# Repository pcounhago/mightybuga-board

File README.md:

# Mighty Bug-A Control board

Control board for the line follower racing car project designed at [A Industriosa](https://intranet.aindustriosa.org/).

## Releases

Version | Description | Status
------------ | ------------- | ------------
[v1](v1/README.md) | Initial board design. Has a mayor supply problem with the AMS1117-3.3 regulator. **Do not use unless you replace the regulator with a more capable one.** | Released
[v1.1](v1.1/README.md) | Updated version of v1 that solves the supply problems by replacing the regulator with a MP2307DN. | Released
[v2](v2/README.md) | Lighter version of the v1.1 redesigned to improve weight distribution in the car. | Released
[v2.1](v2.1/README.md) | Even lighter version of the control board. Include SWIO interface for programming and debug purposes. Fix some minor issues found in v2. | Released

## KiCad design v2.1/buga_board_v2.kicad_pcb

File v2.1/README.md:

# Mighty Bug-A Board v2.1

Control board for the line follower racing car project designed at [A Industriosa](https://intranet.aindustriosa.org/).

* Check the 3D printed chassis designs at [https://gitlab.com/punkto/line_follower_3d_designs](https://gitlab.com/punkto/line_follower_3d_designs)

* For the firmware refer to [https://github.com/hmightypirate/AllMyCircuits](https://github.com/hmightypirate/AllMyCircuits)

## Description

Designed to control a line follower racing car based on differential drive, this board includes an STM32F103 microcontroller coupled with a TB6612FNG dual channel motor driver and a U3V12F9 step-up regulator to power two Pololu micro metal gearmotors at stable 9V. The board provides headers to connect the motors using the magnetic encoder boards mounted on them.

To detect the position of the line, a QTR-8A array featuring 8 Fairchild QRE1113 reflectance sensors is connected to the right angle header mounted on the front.

2 LEDs, 2 push buttons and a buzzer are provided to configure the board and give feedback while the car is on the track.

There is also a UART header that can be used to program the microcontroller and to establish a communication link through cable or Bluetooth if an HC-05 adapter is used.

To expand the capabilities of the board, I2C and SPI buses are available on a header so that other hardware (like an IMU or a slave microcontroller) can be added at any time.

## BOM

Reference | Description | Quantity
------------ | ------------- | ------------- |
BZ1 | MLT-5020 SMD buzzer | 1
C1, C14 | 0805 ceramic capacitor, 1uF | 2
C10, C11 | 0805 ceramic capacitor, 20pF | 2
C12, C13, C15, C16, C17, C19, C21 | 0805 ceramic capacitor, 100nF | 7
C2 | 0805 ceramic capacitor, 10uF | 1
C20, C22 | 0805 ceramic capacitor, 10uF | 2
C3 | 0805 ceramic capacitor, 56nF | 1
C4 | 0805 ceramic capacitor, 100pF | 1
C5 | 0805 ceramic capacitor, 3.9nF | 1
C6 | 10nF | 1
C7 | 15pF | 1
C8 | 22uF | 1
C9, C18 | 4.7uF | 2
D1 | B220A-13-F | 1
D2 | 1210 Green LED | 1
D3 | 1N4148 1210 diode | 1
D4 | 1210 Red LED | 1
D5 | 1210 Blue LED | 1
J1, JP2 | 2 pin 2.54mm vertical header | 2
J2, J6, J7 | JST B6B-ZR connector | 3
J3 | JST S11B-ZR | 1
J4 | JST B4B-ZR | 1
J5 | B5B-ZR | 1
JP1 | 3 pin 2.54mm straight header | 1
L1 | Taiyo Yuden_NR-60xx 4.7uH inductor | 1
L2 | Taiyo Yuden NR-50xx 10uH inductor | 1
Q1, Q2 | SI2369DS P-Channel 30V MOSFET, SOT-23 | 2
Q3 | S8050 NPN Transistor, SOT-23 | 1
R1, R6, R7, R9, R10, R13, R14, R15, R16, R19 | 0805 Resistor, 10k | 10
R11 | 0805 Resistor, 47k | 1
R12 | 0805 Resistor, 7.5k | 1
R17, R18 | 0805 Resistor, 100 | 2
R2, R3, R5, R20 | 0805 Resistor, 100K | 4
R4 | 0805 Resistor, 6.8k | 1
R8 | 0805 Resistor, 26.1k | 1
SW1 | PCM12 SPDT switch | 1
SW2, SW3 | TL3343 Push button | 2
U1 | MP2307DN | 1
U2 | SC4503 | 1
U3 | STM32F103C8T6 | 1
U4 | TB6612FNG | 1
Y1 | 5032 8Mhz crystal | 1

## Acknowledgements

This work was inspired by the great job done in the micromouse maze solving robot Bulebule by [Bulebots](https://github.com/Bulebots):

[https://github.com/Bulebots/bulebule](https://github.com/Bulebots/bulebule)

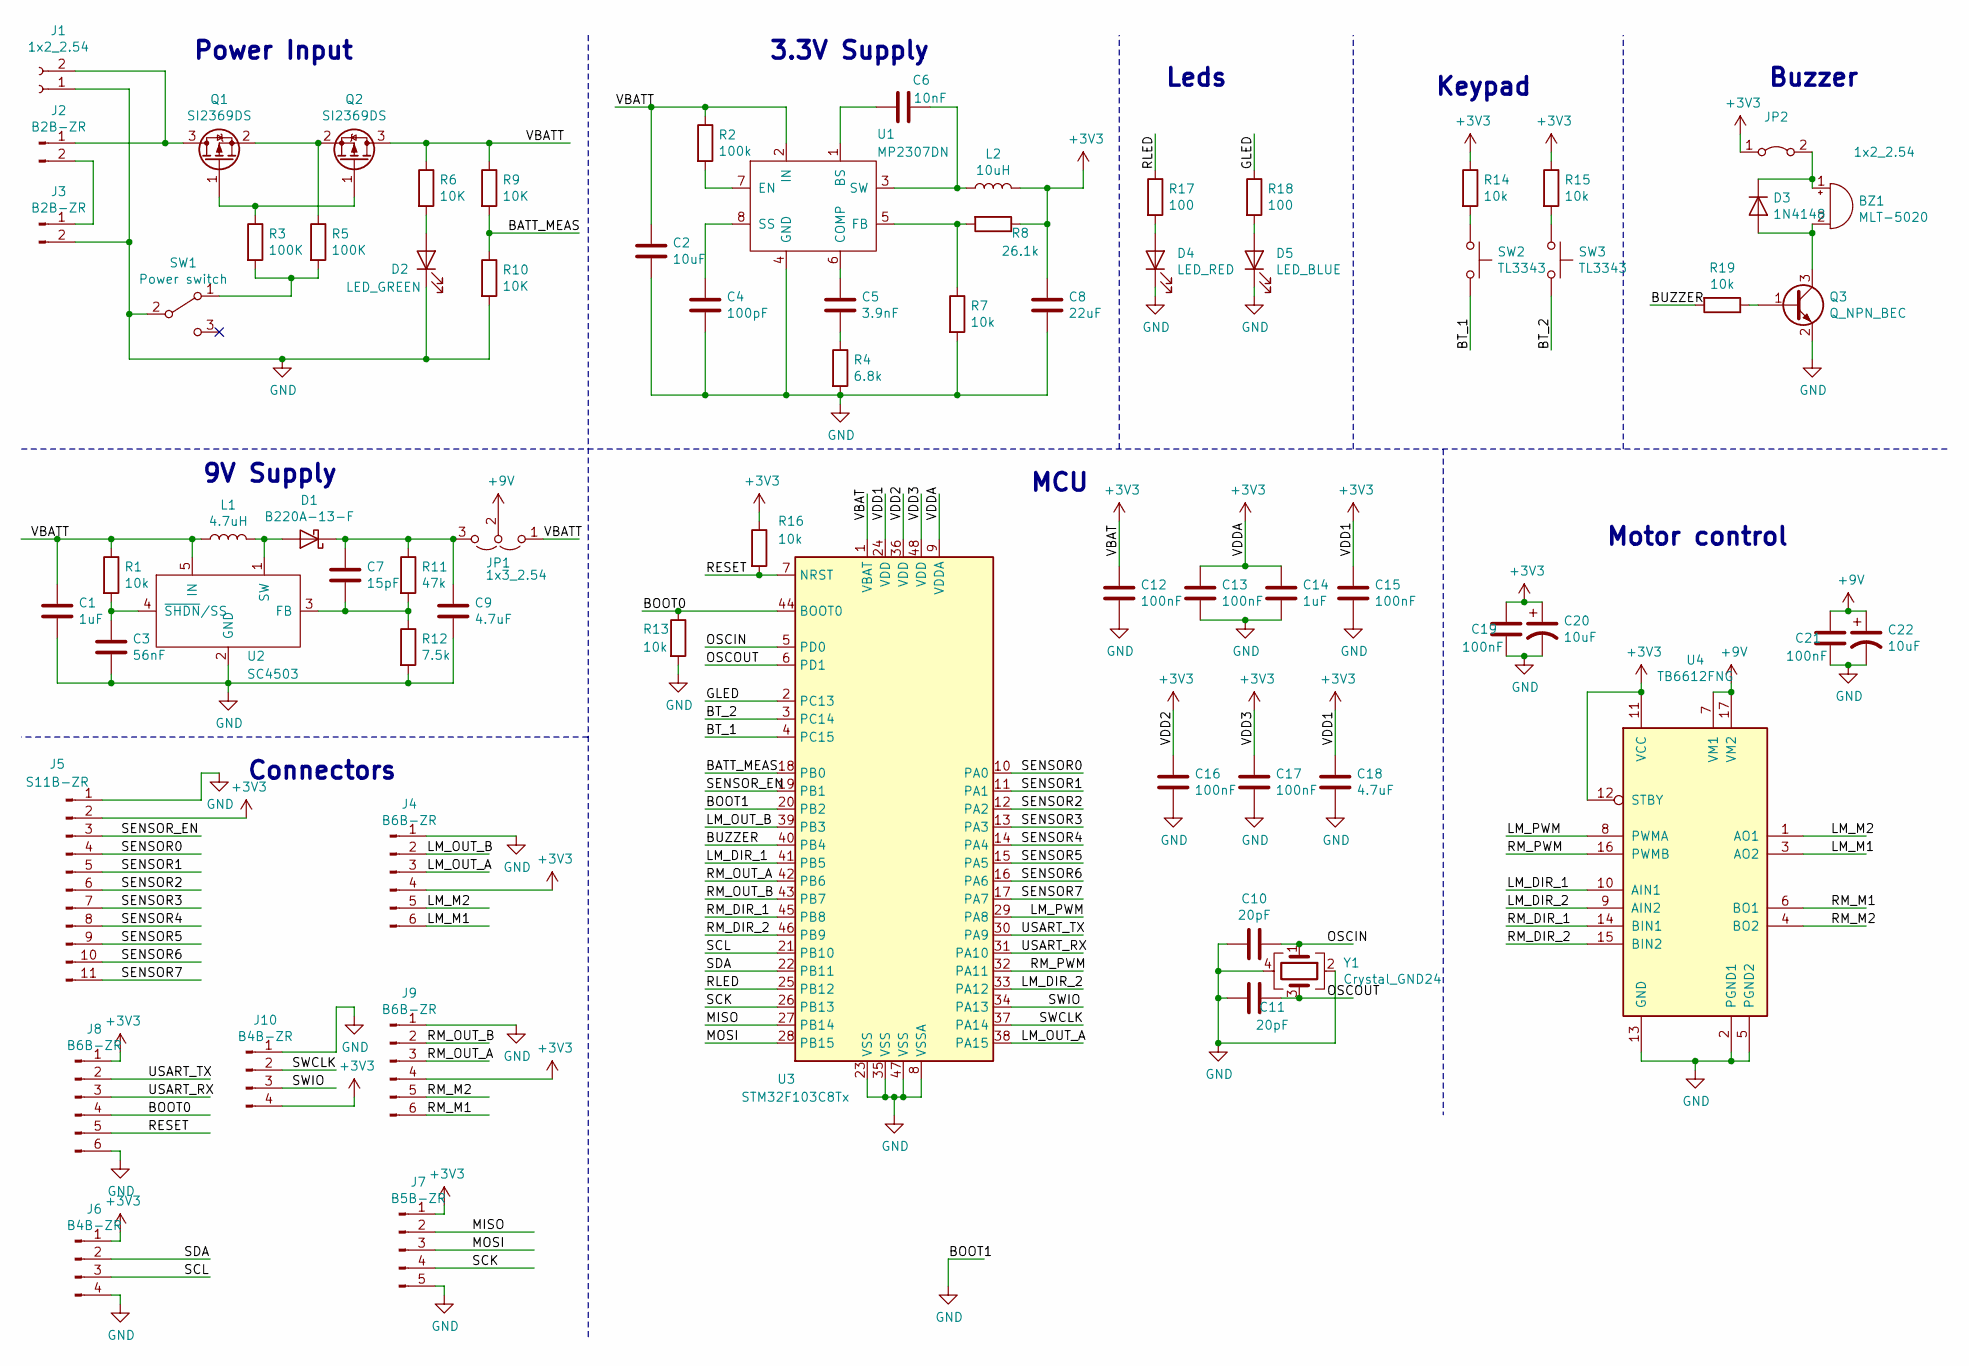
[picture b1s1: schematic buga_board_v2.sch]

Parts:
BZ1: MLT-5020
C1, C14: 1uF; C_0805_2012Metric_Pad1.15x1.40mm_HandSolder
C2: 10uF; C_0805_2012Metric_Pad1.15x1.40mm_HandSolder
C3: 56nF; C_0805_2012Metric_Pad1.15x1.40mm_HandSolder
C4: 100pF; C_0805_2012Metric_Pad1.15x1.40mm_HandSolder
C5: 3.9nF; C_0805_2012Metric_Pad1.15x1.40mm_HandSolder
C6: 10nF; C_0805_2012Metric_Pad1.15x1.40mm_HandSolder
C7: 15pF; C_0805_2012Metric_Pad1.15x1.40mm_HandSolder
C8: 22uF; C_0805_2012Metric_Pad1.15x1.40mm_HandSolder
C9, C18: 4.7uF; C_0805_2012Metric_Pad1.15x1.40mm_HandSolder
C10, C11: 20pF; C_0805_2012Metric_Pad1.15x1.40mm_HandSolder
C12, C13, C15, C16, C17, C19, C21: 100nF; C_0805_2012Metric_Pad1.15x1.40mm_HandSolder
C20, C22: 10uF; L_1210_3225Metric_Pad1.42x2.65mm_HandSolder
D1: B220A-13-F; D_SMA
D2: LED_GREEN; LED_1210_3225Metric_Pad1.42x2.65mm_HandSolder
D3: 1N4148; D_1210_3225Metric_Pad1.42x2.65mm_HandSolder
D4: LED_RED; LED_1210_3225Metric_Pad1.42x2.65mm_HandSolder
D5: LED_BLUE; LED_1210_3225Metric_Pad1.42x2.65mm_HandSolder
J1: 1x2_2.54; PinHeader_1x02_P2.54mm_Vertical
J2, J3: B2B-ZR
J4, J8, J9: B6B-ZR
J5: S11B-ZR
J6, J10: B4B-ZR
J7: B5B-ZR
JP1: 1x3_2.54; PinHeader_1x03_P2.54mm_Vertical
JP2: 1x2_2.54; PinHeader_1x02_P2.54mm_Vertical
L1: 4.7uH; L_Taiyo-Yuden_NR-60xx
L2: 10uH; L_Taiyo-Yuden_NR-50xx
Q1, Q2: SI2369DS; SOT-23
Q3: Q_NPN_BEC; SOT-23
R1, R7, R13, R14, R15, R16, R19: 10k; R_0805_2012Metric_Pad1.15x1.40mm_HandSolder
R2: 100k; R_0805_2012Metric_Pad1.15x1.40mm_HandSolder
R3, R5: 100K; R_0805_2012Metric_Pad1.15x1.40mm_HandSolder
R4: 6.8k; R_0805_2012Metric_Pad1.15x1.40mm_HandSolder
R6, R9, R10: 10K; R_0805_2012Metric_Pad1.15x1.40mm_HandSolder
R8: 26.1k; R_0805_2012Metric_Pad1.15x1.40mm_HandSolder
R11: 47k; R_0805_2012Metric_Pad1.15x1.40mm_HandSolder
R12: 7.5k; R_0805_2012Metric_Pad1.15x1.40mm_HandSolder
R17, R18: 100; R_0805_2012Metric_Pad1.15x1.40mm_HandSolder
SW1: Power switch; SW_SPDT_PCM12
SW2, SW3: TL3343; SW_SPST_TL3342
U1: MP2307DN; SOIC-8-1EP_3.9x4.9mm_P1.27mm_EP2.35x2.35mm
U2: SC4503; TSOT-23-5
U3: STM32F103C8Tx; LQFP-48_7x7mm_P0.5mm
U4: TB6612FNG; tb6612fng
Y1: Crystal_GND24; Crystal_SMD_5032-4Pin_5.0x3.2mm

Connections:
+3V3: C8.1, C12.1, C13.1, C14.1, C15.1, C16.1, C17.1, C18.1, C19.1, C20.1, J4.4, J5.2, J6.1, J7.1, J8.1, J9.4, J10.4, JP2.1 (A), L2.2, R8.1, R14.1, R15.1, R16.1, U3.1 (VBAT), U3.9 (VDDA), U3.24 (VDD), U3.36 (VDD), U3.48 (VDD), U4.11 (VCC), U4.12 (STBY)
+9V: C21.1, C22.1, JP1.2 (C), U4.7 (VM1), U4.17 (VM2)
/BATT_MEAS: R9.2, R10.1, U3.18 (PB0)
/BOOT0: J8.4, R13.1, U3.44 (BOOT0)
/BT_1: SW2.2, U3.4 (PC15)
/BT_2: SW3.2, U3.3 (PC14)
/BUZZER: R19.2, U3.40 (PB4)
/GLED: R18.1, U3.2 (PC13)
/LM_DIR_1: U3.41 (PB5), U4.10 (AIN1)
/LM_DIR_2: U3.33 (PA12), U4.9 (AIN2)
/LM_M1: J4.6, U4.3 (AO2)
/LM_M2: J4.5, U4.1 (AO1)
/LM_OUT_A: J4.3, U3.38 (PA15)
/LM_OUT_B: J4.2, U3.39 (PB3)
/LM_PWM: U3.29 (PA8), U4.8 (PWMA)
/MISO: J7.2, U3.27 (PB14)
/MOSI: J7.3, U3.28 (PB15)
/OSCIN: C10.1, U3.5 (PD0), Y1.1
/OSCOUT: C11.1, U3.6 (PD1), Y1.3
/RESET: J8.5, R16.2, U3.7 (NRST)
/RLED: R17.1, U3.25 (PB12)
/RM_DIR_1: U3.45 (PB8), U4.14 (BIN1)
/RM_DIR_2: U3.46 (PB9), U4.15 (BIN2)
/RM_M1: J9.6, U4.6 (BO1)
/RM_M2: J9.5, U4.4 (BO2)
/RM_OUT_A: J9.3, U3.42 (PB6)
/RM_OUT_B: J9.2, U3.43 (PB7)
/RM_PWM: U3.32 (PA11), U4.16 (PWMB)
/SCK: J7.4, U3.26 (PB13)
/SCL: J6.3, U3.21 (PB10)
/SDA: J6.2, U3.22 (PB11)
/SENSOR0: J5.4, U3.10 (PA0)
/SENSOR1: J5.5, U3.11 (PA1)
/SENSOR2: J5.6, U3.12 (PA2)
/SENSOR3: J5.7, U3.13 (PA3)
/SENSOR4: J5.8, U3.14 (PA4)
/SENSOR5: J5.9, U3.15 (PA5)
/SENSOR6: J5.10, U3.16 (PA6)
/SENSOR7: J5.11, U3.17 (PA7)
/SENSOR_EN: J5.3, U3.19 (PB1)
/SWCLK: J10.2, U3.37 (PA14)
/SWIO: J10.3, U3.34 (PA13)
/USART_RX: J8.3, U3.31 (PA10)
/USART_TX: J8.2, U3.30 (PA9)
/VBATT: C1.1, C2.1, JP1.1 (A), L1.1, Q2.3 (D), R1.1, R2.1, R6.1, R9.1, U1.2 (IN), U2.5 (IN)
GND: C1.2, C2.2, C3.2, C4.2, C8.2, C9.2, C10.2, C11.2, C12.2, C13.2, C14.2, C15.2, C16.2, C17.2, C18.2, C19.2, C20.2, C21.2, C22.2, D2.1 (K), D4.1 (K), D5.1 (K), J1.1, J3.2, J4.1, J5.1, J6.4, J7.5, J8.6, J9.1, J10.1, Q3.2 (E), R4.2, R7.2, R10.2, R12.2, R13.2, SW1.2 (B), U1.4 (GND), U2.2 (GND), U3.8 (VSSA), U3.20 (PB2), U3.23 (VSS), U3.35 (VSS), U3.47 (VSS), U4.2 (PGND1), U4.5 (PGND2), U4.13 (GND), Y1.2, Y1.4
unnamed: BZ1.1 (-), D3.1 (K), JP2.2 (B)
unnamed: BZ1.2 (+), D3.2 (A), Q3.3 (C)
unnamed: C3.1, R1.2, U2.4 (~SHDN~/SS)
unnamed: C4.1, U1.8 (SS)
unnamed: C5.1, U1.6 (COMP)
unnamed: C5.2, R4.1
unnamed: C6.1, L2.1, U1.3 (SW)
unnamed: C6.2, U1.1 (BS)
unnamed: C7.1, C9.1, D1.1 (K), JP1.3 (B), R11.1
unnamed: C7.2, R11.2, R12.1, U2.3 (FB)
unnamed: D1.2 (A), L1.2, U2.1 (SW)
unnamed: D2.2 (A), R6.2
unnamed: D4.2 (A), R17.2
unnamed: D5.2 (A), R18.2
unnamed: J1.2, J2.1, Q1.3 (D)
unnamed: J2.2, J3.1
unnamed: Q1.1 (G), Q2.1 (G), R3.1
unnamed: Q1.2 (S), Q2.2 (S), R5.1
unnamed: Q3.1 (B), R19.1
unnamed: R2.2, U1.7 (EN)
unnamed: R3.2, R5.2, SW1.1 (A)
unnamed: R7.1, R8.2, U1.5 (FB)
unnamed: R14.2, SW2.1
unnamed: R15.2, SW3.1

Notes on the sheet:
Power Input
9V Supply
3.3V Supply
Motor control
Buzzer
Keypad
Leds
MCU
Connectors

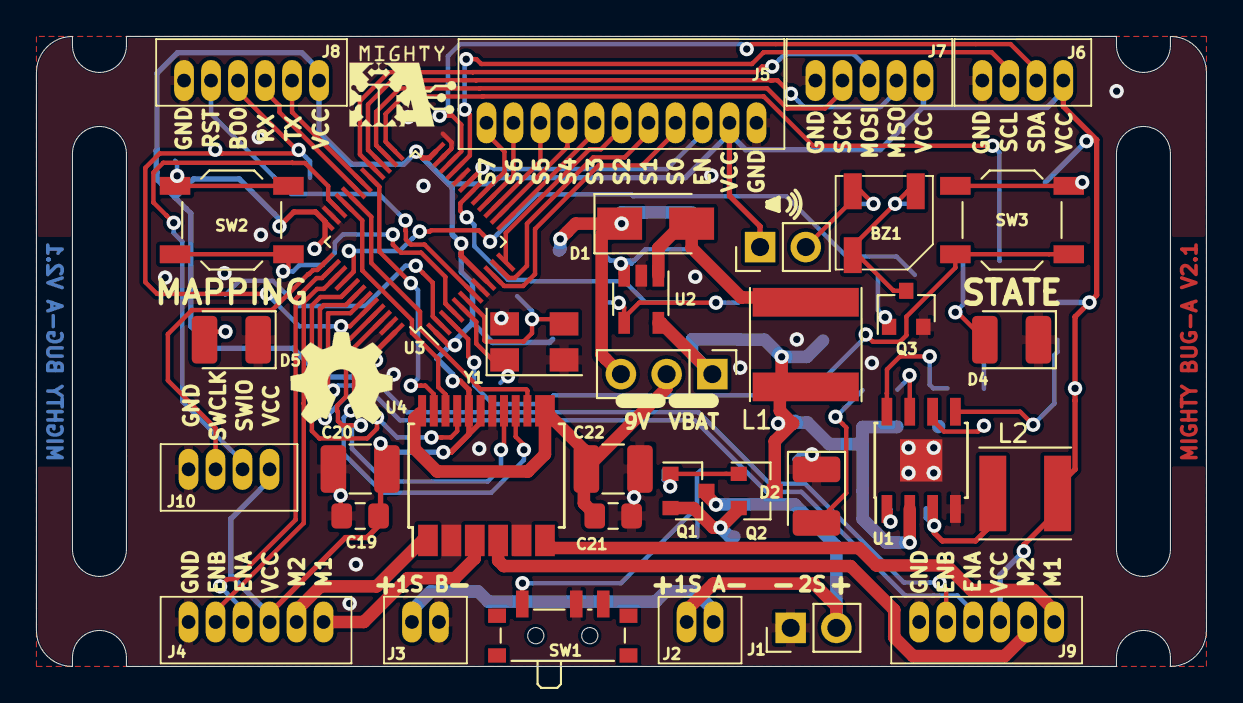
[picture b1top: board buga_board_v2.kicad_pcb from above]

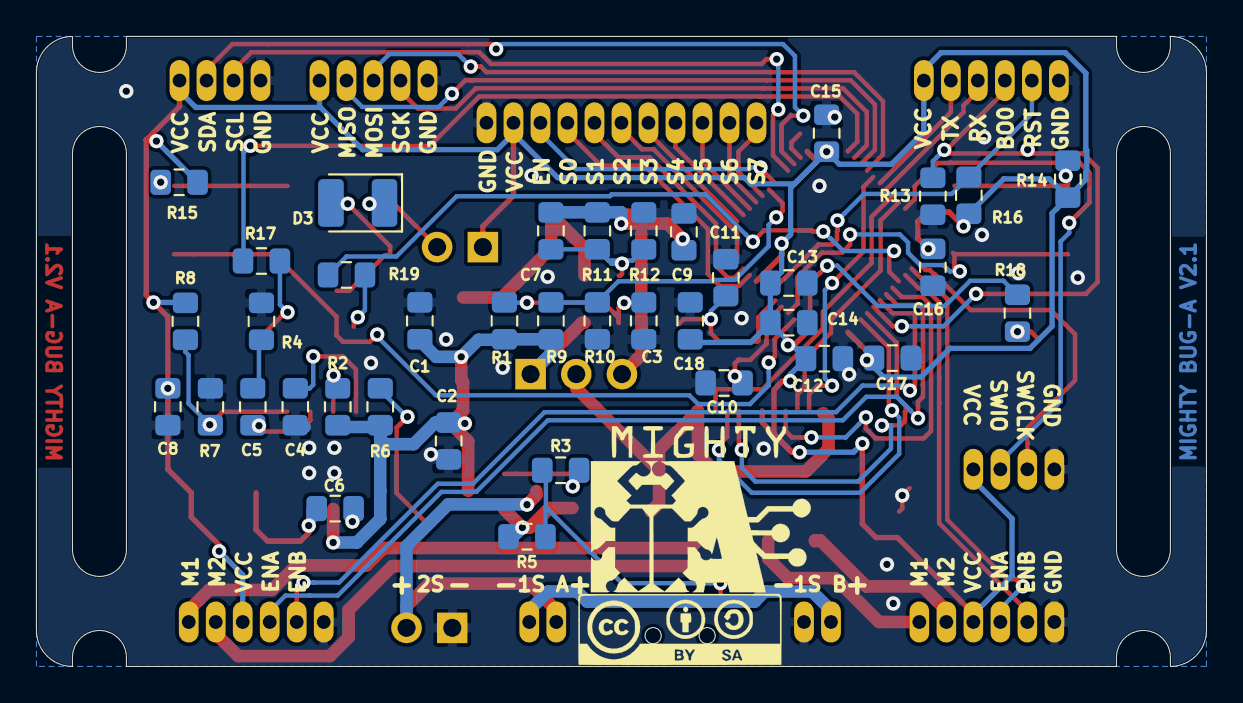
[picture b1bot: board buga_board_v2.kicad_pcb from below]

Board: 2 copper layers, 65.0 x 35.0 mm, 72 parts (38 on the bottom side), 70 nets.

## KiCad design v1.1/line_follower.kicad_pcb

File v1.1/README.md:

# Mighty Bug-A Board v1.1

Control board for the line follower racing car project designed at [A Industriosa](https://intranet.aindustriosa.org/).

* Check the 3D printed chassis designs at [https://gitlab.com/punkto/line_follower_3d_designs](https://gitlab.com/punkto/line_follower_3d_designs)

* For the firmware refer to [https://github.com/hmightypirate/AllMyCircuits](https://github.com/hmightypirate/AllMyCircuits)

## Description

Designed to control a line follower racing car based on differential drive, this board includes an STM32F103 microcontroller coupled with a TB6612FNG dual channel motor driver and a U3V12F9 step-up regulator to power two Pololu micro metal gearmotors at stable 9V. The board provides headers to connect the motors using the magnetic encoder boards mounted on them.

To detect the position of the line, a QTR-8A array featuring 8 Fairchild QRE1113 reflectance sensors is connected to the right angle header mounted on the front.

2 LEDs, 3 push buttons and a buzzer are provided to configure the board and give feedback while the car is on the track.

There is also a UART header that can be used to program the microcontroller and to establish a communication link through cable or Bluetooth if an HC-05 adapter is used.

To expand the capabilities of the board, I2C and SPI buses are available on a header so that other hardware (like an IMU or a slave microcontroller) can be added at any time.

**This board solves the problem with the regulator found in the previous version. By replacing the AMS1117-3.3 with a MP2307DN, the board can easily handle the regulation from the 8.4V provided by the battery when fully charged to the 3.3V required by the electronics.**

## BOM

Item | Description | Quantity
------------ | ------------- | ------------- |
Bluepill | STM32F103 microcontroller board | 1
MP2307DN | 3.3V Step-down voltage regulator. Can be found with the name Mini-360 in chinese stores. | 1
U3V12F9 | 9V Step-up regulator board from Pololu | 1
Buzzer | Passive buzzer board | 1
TB6612FNG | 2 Channel motor driver board | 1
5 mm LED | 5mm LEDs of different colors | 2
Push button | Through hole push buttons | 3
100Ω Resistor | Through hole resistors | 5
47kΩ Resistor | Through hole resistors | 1
20kΩ Resistor | Through hole resistors | 1
40x1 Female socket 2.54mm pitch | Female socket to plug, the bluepill, the motor driver and the Bluetooth module to the board | 1
40x1 Male pin 2.54mm pitch | Male pin strip to plug the motors, the battery, the expansion boards and the jumper to the board | 1
40x1 Right angle male pin 2.54mm pitch | Male pin strip to connect the reflectance sensor array to the board | 1
33uF Capacitor | Electrolytic capacitor to connect to the output of the step up regulator | 1

## Acknowledgements

This work was inspired by the great job done in the micromouse maze solving robot Bulebule by [Bulebots](https://github.com/Bulebots):

[https://github.com/Bulebots/bulebule](https://github.com/Bulebots/bulebule)

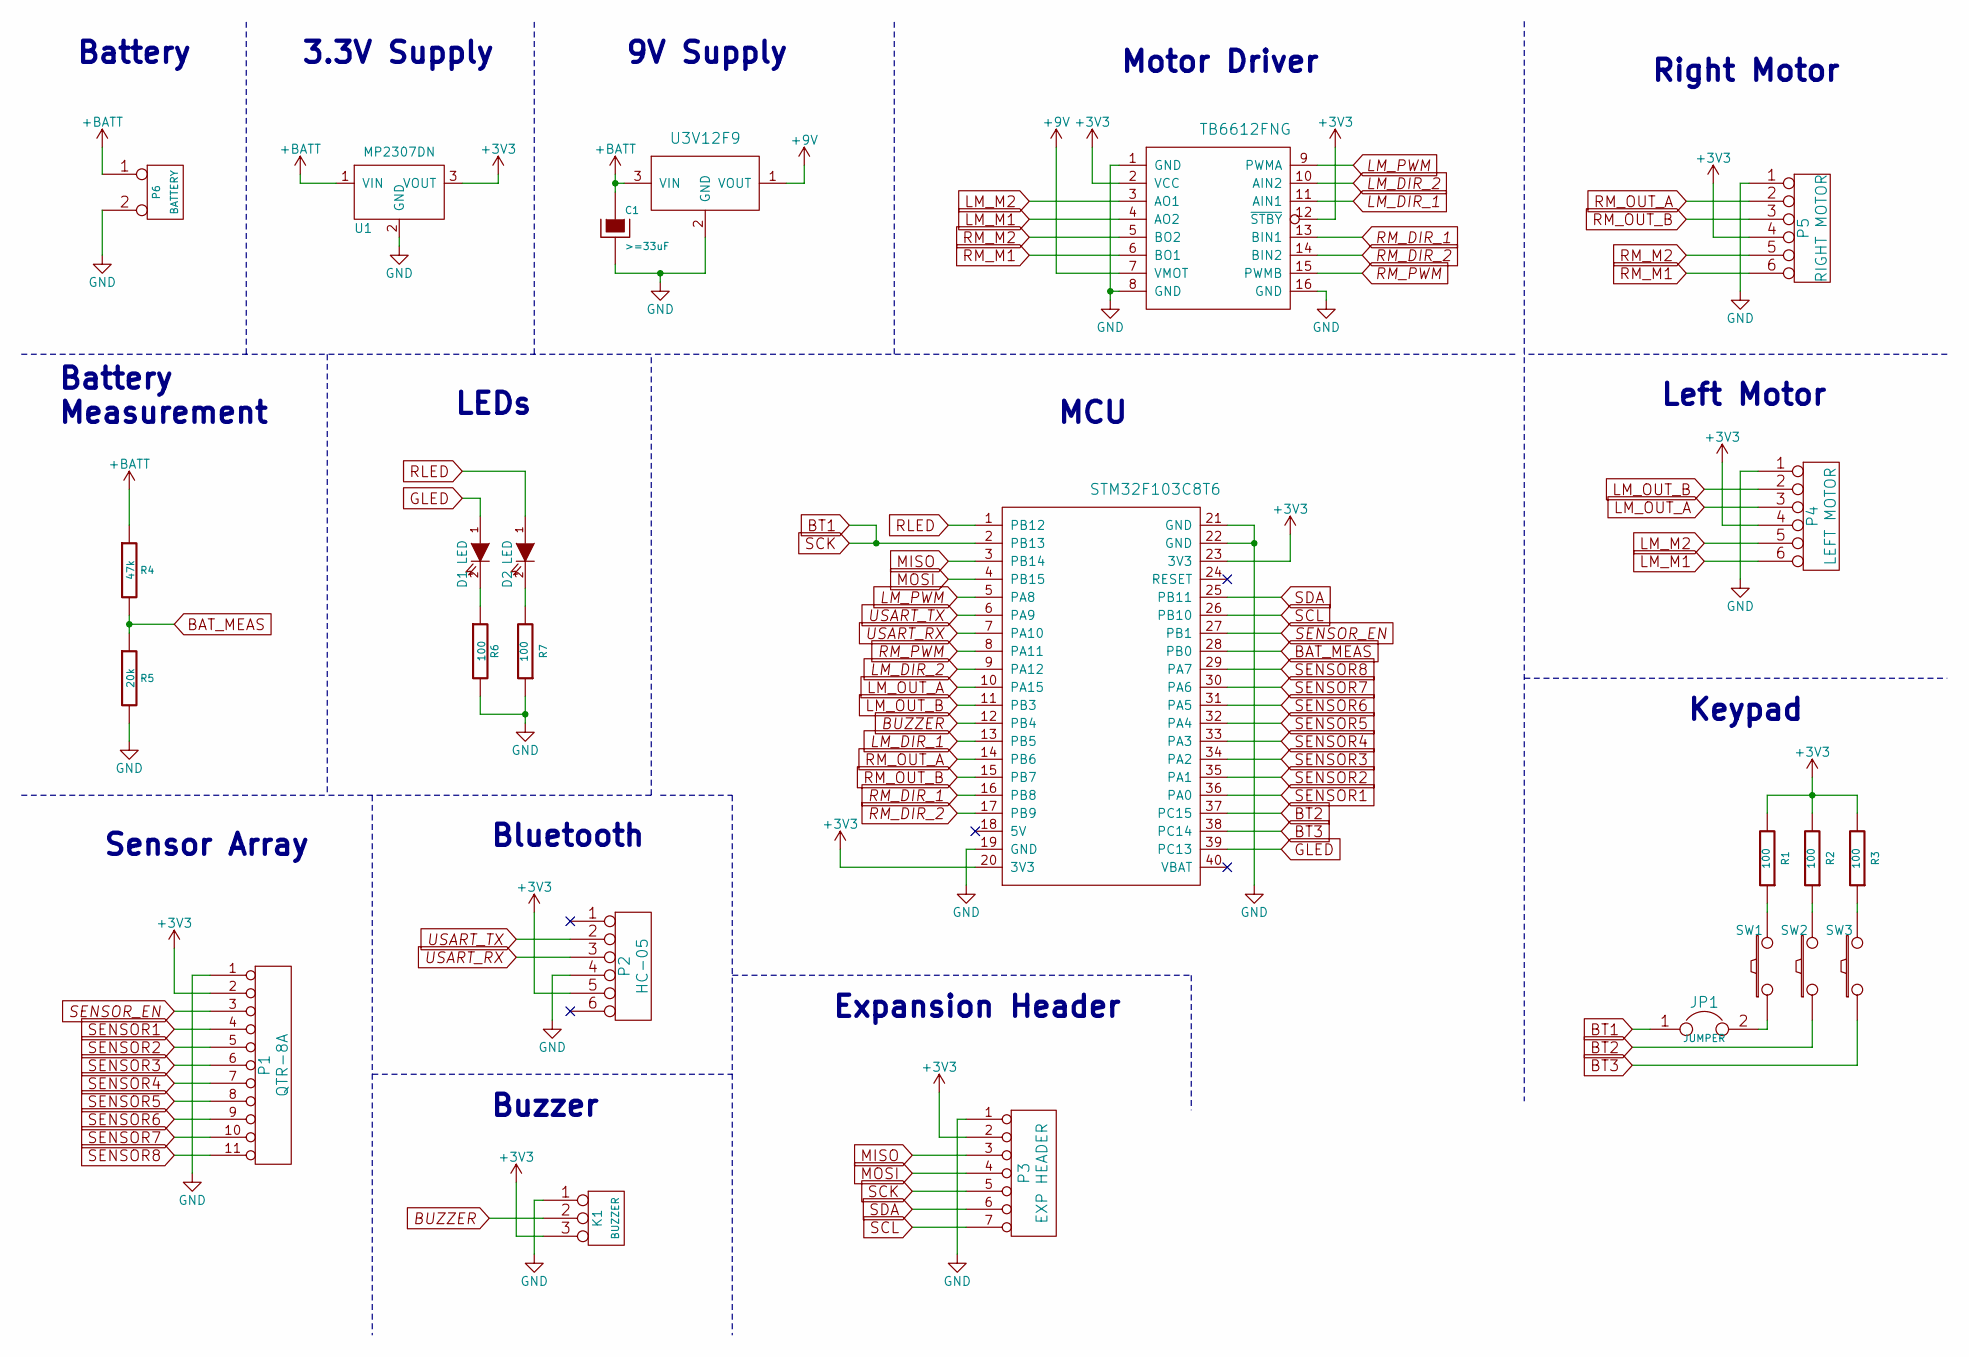
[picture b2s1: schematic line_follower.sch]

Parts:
C1: >=33uF; CP_Radial_D6.3mm_P2.50mm
D1, D2: LED; LED_D5.0mm
JP1: JUMPER; Pin_Header_Straight_1x02_Pitch2.54mm
K1: BUZZER; Buzzer
P1: QTR-8A; Pin_Header_Straight_1x11_Pitch2.54mm
P2: HC-05
P3: EXP HEADER; Header
P4: LEFT MOTOR; pololu_magnetic_encoder
P5: RIGHT MOTOR; pololu_magnetic_encoder
P6: BATTERY; 2S_LiPo
R1, R2, R3, R6, R7: 100; R_Axial_DIN0204_L3.6mm_D1.6mm_P7.62mm_Horizontal
R4: 47k; R_Axial_DIN0204_L3.6mm_D1.6mm_P7.62mm_Horizontal
R5: 20k; R_Axial_DIN0204_L3.6mm_D1.6mm_P7.62mm_Horizontal
SW1, SW2, SW3: SW_PUSH; SW_PUSH_6mm_h5mm
U1: MP2307DN
U2: U3V12F9; u3v12f9
U6: STM32F103C8T6; BluePill_STM32F103C
U7: TB6612FNG; tb6612fng_sparkfun

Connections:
+3V3: K1.3, P1.2, P2.5, P3.2, P4.4, P5.4, R1.2, R2.2, R3.2, U1.3 (VOUT), U6.20 (3V3), U6.23 (3V3), U7.2 (VCC), U7.12 (~STBY~)
+9V: U2.1 (VOUT), U7.7 (VMOT)
+BATT: C1.1, P6.1, R4.1, U1.1 (VIN), U2.3 (VIN)
BAT_MEAS: R4.2, R5.1, U6.28 (PB0)
BT1: JP1.1, P3.5, U6.2 (PB13)
BT2: SW2.1, U6.37 (PC15)
BT3: SW3.1, U6.38 (PC14)
BUZZER: K1.2 (PM), U6.12 (PB4)
GLED: D1.1 (A), U6.39 (PC13)
GND: C1.2, K1.1, P1.1, P2.4, P3.1, P4.1, P5.1, P6.2 (PM), R5.2, R6.2, R7.1, U1.2 (GND), U2.2 (GND), U6.19 (GND), U6.21 (GND), U6.22 (GND), U7.1 (GND), U7.8 (GND), U7.16 (GND)
LM_DIR_1: U6.13 (PB5), U7.11 (AIN1)
LM_DIR_2: U6.9 (PA12), U7.10 (AIN2)
LM_M1: P4.5, U7.3 (AO1)
LM_M2: P4.6, U7.4 (AO2)
LM_OUT_A: P4.3, U6.10 (PA15)
LM_OUT_B: P4.2, U6.11 (PB3)
LM_PWM: U6.5 (PA8), U7.9 (PWMA)
MISO: P3.3, U6.3 (PB14)
MOSI: P3.4, U6.4 (PB15)
unnamed: D1.2 (K), R6.1
unnamed: D2.2 (K), R7.2
unnamed: JP1.2, SW1.1
unnamed: R1.1, SW1.2
unnamed: R2.1, SW2.2
unnamed: R3.1, SW3.2
RLED: D2.1 (A), U6.1 (PB12)
RM_DIR_1: U6.16 (PB8), U7.13 (BIN1)
RM_DIR_2: U6.17 (PB9), U7.14 (BIN2)
RM_M1: P5.5, U7.5 (BO2)
RM_M2: P5.6, U7.6 (BO1)
RM_OUT_A: P5.2, U6.14 (PB6)
RM_OUT_B: P5.3, U6.15 (PB7)
RM_PWM: U6.8 (PA11), U7.15 (PWMB)
SCL: P3.7, U6.26 (PB10)
SDA: P3.6, U6.25 (PB11)
SENSOR1: P1.4, U6.36 (PA0)
SENSOR2: P1.5, U6.35 (PA1)
SENSOR3: P1.6, U6.34 (PA2)
SENSOR4: P1.7, U6.33 (PA3)
SENSOR5: P1.8, U6.32 (PA4)
SENSOR6: P1.9, U6.31 (PA5)
SENSOR7: P1.10, U6.30 (PA6)
SENSOR8: P1.11, U6.29 (PA7)
SENSOR_EN: P1.3, U6.27 (PB1)
USART_RX: P2.3, U6.7 (PA10)
USART_TX: P2.2, U6.6 (PA9)

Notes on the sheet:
Right Motor
Left Motor
Motor Driver
Keypad
9V Supply
3.3V Supply
Battery
Battery Measurement
LEDs
Sensor Array
Bluetooth
Buzzer
Expansion Header
MCU

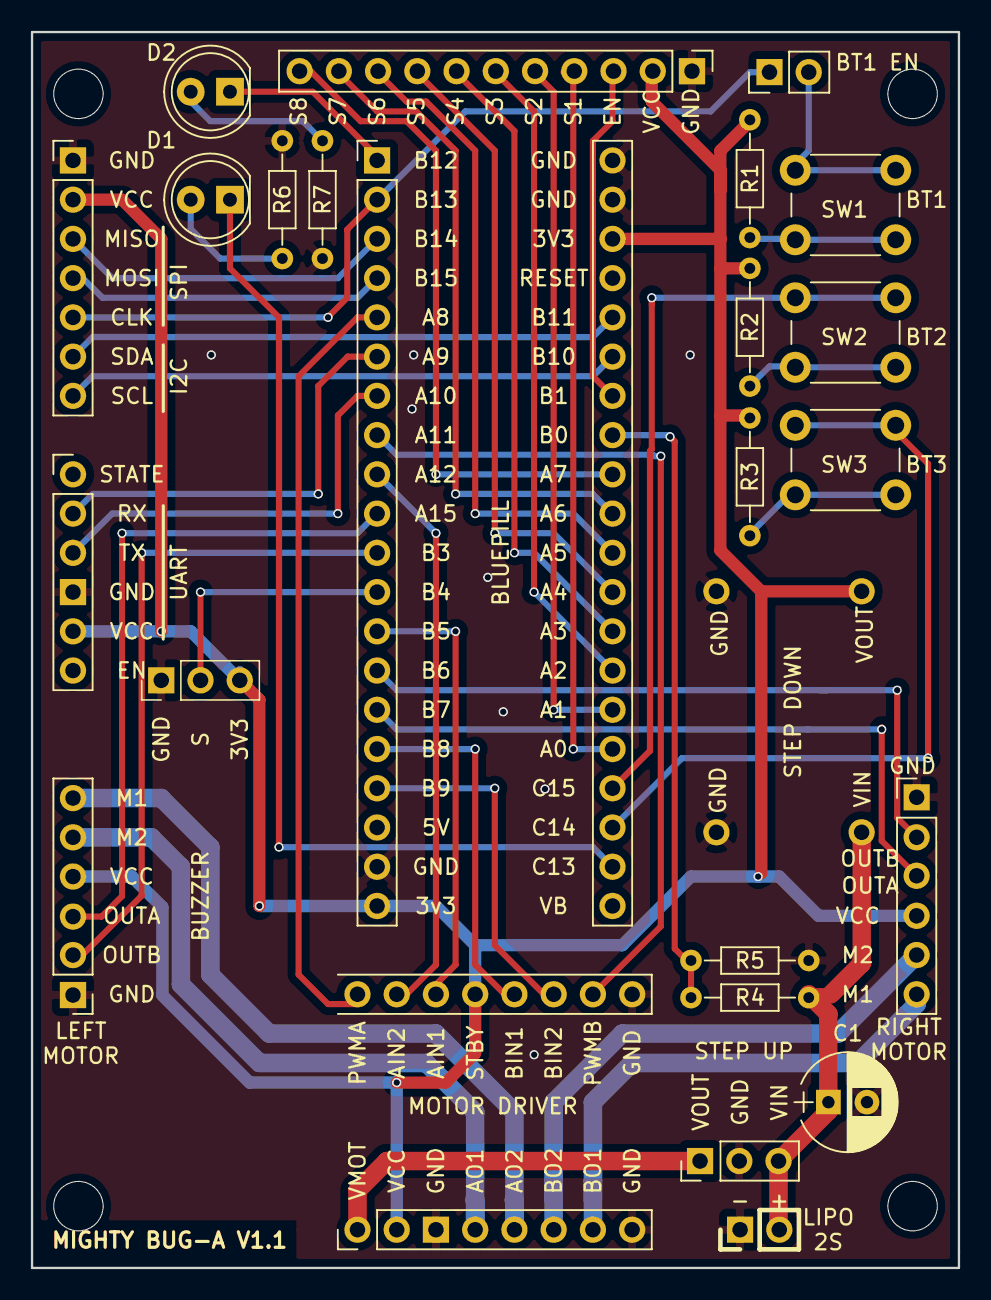
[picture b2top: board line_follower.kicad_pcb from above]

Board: 2 copper layers, 60.0 x 80.0 mm, 25 parts (0 on the bottom side), 46 nets.

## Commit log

2019-01-28 Add board v1 to the repository
2019-01-29 Add initial README and move LICENSE to root folder
2019-01-29 Add missing graphics and mounting holes
2019-01-30 Add board version v1.1
2019-01-30 Fix error in README.md
2019-10-14 Small cosmetic changes. Include schematic in PNG format.
2019-10-14 Add schematic in PNG format for v1 board.
2019-10-14 Remove duplicate LICENSE file.
2019-10-16 Release V2 board
2019-10-17 Release v2.1 board
